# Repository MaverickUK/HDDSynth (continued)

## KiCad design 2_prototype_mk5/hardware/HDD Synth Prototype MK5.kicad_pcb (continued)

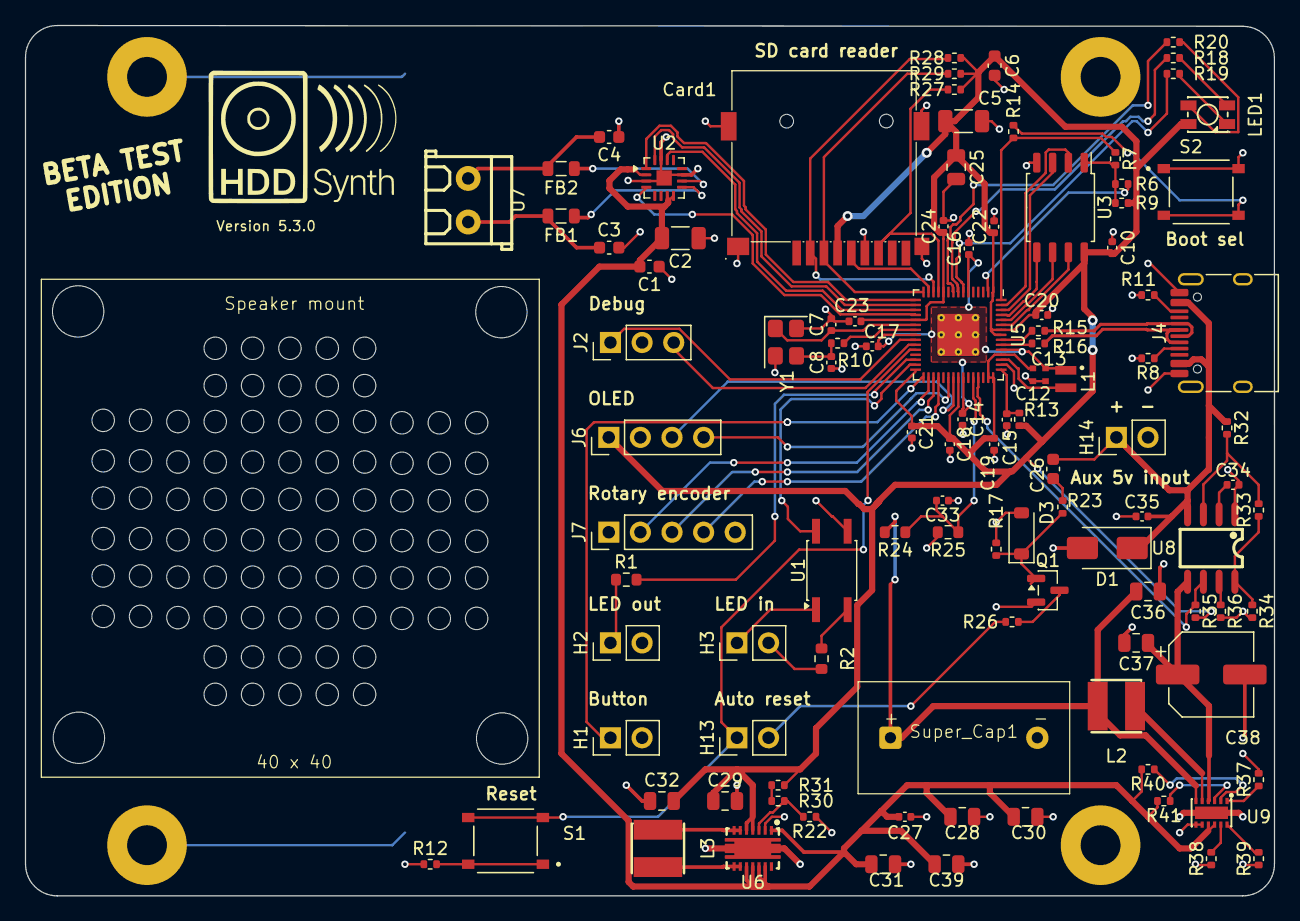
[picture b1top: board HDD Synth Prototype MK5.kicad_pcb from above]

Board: 2 copper layers, 100.3 x 69.9 mm, 110 parts (1 on the bottom side), 81 nets.

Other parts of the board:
 : LOGO; MHDDLA_Sound_40mm

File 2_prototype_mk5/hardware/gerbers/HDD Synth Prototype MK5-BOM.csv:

"Reference","Qty","Value","DNP","Exclude from BOM","Exclude from Board","LCSC Part Number","Footprint","Datasheet","Description"
"C1,C6,C26","3","0.1uF","","","","C14663","Capacitor_SMD:C_0603_1608Metric","","Unpolarized capacitor"
"C2,C5","2","10uF","","","","C13585","Capacitor_SMD:C_1206_3216Metric","","Unpolarized capacitor"
"C3,C4","2","1nF","","","","C1588","Capacitor_SMD:C_0603_1608Metric","","Unpolarized capacitor, small symbol"
"C7,C8","2","15p","","","","C1548","Capacitor_SMD:C_0402_1005Metric","",""
"C10,C14,C17,C18,C19,C20,C21,C22,C23,C24,C27,C33","12","100nF","","","","C1525","Capacitor_SMD:C_0402_1005Metric","",""
"C12,C13","2","4.7uF","","","","C23733","RP2350:C_0402_1005Metric_small_pads","",""
"C15,C16","2","4.7uF","","","","C23733","Capacitor_SMD:C_0402_1005Metric","",""
"C25,C28,C30,C36,C37","5","10uF","","","","C15850","Capacitor_SMD:C_0805_2012Metric","",""
"C29,C31,C32,C39","4","22uF","","","","C45783","Capacitor_SMD:C_0805_2012Metric","",""
"C34","1","4.7nF","","","","","Capacitor_SMD:C_0402_1005Metric","",""
"C35","1","1uF","","","","","Capacitor_SMD:C_0402_1005Metric","",""
"C38","1","100uF","","","","C134801","Capacitor_SMD:CP_Elec_6.3x7.7","","Polarized capacitor"
"Card1","1","TF-015","","","","C113206","easyeda2kicad:TF-SMD_TF-015","https://lcsc.com/product-detail/Card-Sockets_TF-015_C113206.html",""
"D1","1","SMAJ5.0A","","","","","Diode_SMD:D_SMA","","Zener diode"
"D3","1","1N4148W","","","","C81598","Diode_SMD:D_SOD-123","https://www.vishay.com/docs/85748/1n4148w.pdf","75V 0.15A Fast Switching Diode, SOD-123"
"FB1,FB2","2","FerriteBead_Small","","","","C85840","Inductor_SMD:L_0805_2012Metric","","Ferrite bead, small symbol"
"H1,H2,H3,H13,H14","5","Conn_01x02","","","","C124375","Connector_PinHeader_2.54mm:PinHeader_1x02_P2.54mm_Vertical","","Generic connector, single row, 01x02, script generated (kicad-library-utils/schlib/autogen/connector/)"
"J2","1","Conn_01x03","","","","C49257","Connector_PinHeader_2.54mm:PinHeader_1x03_P2.54mm_Vertical","","Generic connector, single row, 01x03, script generated (kicad-library-utils/schlib/autogen/connector/)"
"J4","1","USB_C_Receptacle_USB2.0_16P","","","","C165948","Connector_USB:USB_C_Receptacle_HRO_TYPE-C-31-M-12","","USB 2.0-only 16P Type-C Receptacle connector"
"J6","1","Conn_01x04_Pin","","","","C124378","Connector_PinHeader_2.54mm:PinHeader_1x04_P2.54mm_Vertical","","Generic connector, single row, 01x04, script generated"
"J7","1","Conn_01x05","","","","C124379","Connector_PinHeader_2.54mm:PinHeader_1x05_P2.54mm_Vertical","","Generic connector, single row, 01x05, script generated (kicad-library-utils/schlib/autogen/connector/)"
"L1","1","3.3u","","","","C42411119","RP2350:L_pol_2016","",""
"L2","1","2.2 µH","","","","C167804","easyeda2kicad:IND-SMD_L4.0-W4.0_FNR40XXS","","Inductor"
"L3","1","FNR4018S1R5MT","","","","C167802","easyeda2kicad:IND-SMD_L4.0-W4.0_FNR40XXS","https://lcsc.com/product-detail/Power-Inductors_1-5uH-20_C16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",""
"LED1","1","XL-3528RGBW-HM","","","","C2843813","Custom:LED-SMD_4P-L3.2-W2.8-LS3.5-XL-3528RGBW-HM5","https://www.lcsc.com/datasheet/C2843813.pdf",""
"Q1","1","2N7002","","","","C8545","Package_TO_SOT_SMD:SOT-23","https://www.onsemi.com/pub/Collateral/NDS7002A-D.PDF","0.115A Id, 60V Vds, N-Channel MOSFET, SOT-23"
"R1,R2","2","330R","","","","C23138","Resistor_SMD:R_0603_1608Metric","","Resistor"
"R7","1","0","","","","C17168","Resistor_SMD:R_0402_1005Metric","",""
"R8,R11","2","5.1K","","","","C25905","Resistor_SMD:R_0402_1005Metric","","Resistor"
"R10,R12,R14,R26","4","1K","","","","C11702","Resistor_SMD:R_0402_1005Metric","","Resistor"
"R13,R18,R20","3","33R","","","","C25105","Resistor_SMD:R_0402_1005Metric","","Resistor"
"R15,R16","2","27R","","","","C25100","Resistor_SMD:R_0402_1005Metric","",""
"R17,R30,R40,R41","4","100K","","","","C25741","Resistor_SMD:R_0402_1005Metric","","Resistor"
"R19","1","200R","","","","C25087","Resistor_SMD:R_0402_1005Metric","","Resistor"
"R22","1","22K","","","","C25768","Resistor_SMD:R_0402_1005Metric","","Resistor"
"R23,R35","2","10K","","","","C25744","Resistor_SMD:R_0402_1005Metric","","Resistor"
"R24,R25","2","22K","","","","C31850","Resistor_SMD:R_0603_1608Metric","","Resistor"
"R27,R28,R29,R33","4","47K","","","","C25792","Resistor_SMD:R_0402_1005Metric","","Resistor"
"R31","1","24K","","","","C25769","Resistor_SMD:R_0402_1005Metric","","Resistor"
"R32","1","330K","","","","C25778","Resistor_SMD:R_0402_1005Metric","","Resistor"
"R34","1","120K","","","","C25750","Resistor_SMD:R_0402_1005Metric","","Resistor"
"R36","1","110K","","","","C2909311","Resistor_SMD:R_0402_1005Metric","","Resistor"
"R37,R38,R39","3","75K","","","","C25798","Resistor_SMD:R_0402_1005Metric","","Resistor"
"S1,S2","2","TS-1187A-B-A-B","","","","C318884","Custom:SW_TS-1187A-B-A-B","","Tactile Switch SPST 160gf 1.5mm 5.1mm x 5.1mm Surface Mount"
"U1","1","Optocoupler_DC_PhotoNPN_AKEC","","","","C42381015","Package_SO:SO-4_4.4x3.6mm_P2.54mm","","Generic DC optocoupler with NPN phototransistor output, pins order: anode/cathode/emitter/collector"
"U2","1","MAX98357A","","","","C910544","Package_DFN_QFN:TQFN-16-1EP_3x3mm_P0.5mm_EP1.23x1.23mm","https://www.analog.com/media/en/technical-documentation/data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","Mono DAC with amplifier, I2S, PCM, TDM, 32-bit, 96khz, 3.2W, TQFP-16"
"U5","1","RP2350_60QFN","","","","C41378174","RP2350:RP2350-QFN-60-1EP_7x7_P0.4mm_EP3.4x3.4mm_ThermalVias","",""
"U6","1","TPS63020DSJR","","","","C15483","easyeda2kicad:VSON-14_L4.0-W3.0-P0.50-BL-EP_TI_DSJ","https://lcsc.com/product-detail/DC-DC-Converters_TI_TPS63020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",""
"U7","1","KF350-3.5-2P","","","","C474892","easyeda2kicad:CONN-TH_P3.50_KF350-3.5-2P","https://lcsc.com/product-detail/New-Quadratic-Unclassified-D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",""
"U8","1","TPS25921ADR","","","","C189199","easyeda2kicad:SOIC-8_L5.0-W4.0-P1.27-LS6.0-BL","https://lcsc.com/product-detail/PMIC-Supervisors_TI_TPS25921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",""
"U9","1","TPS61094DSSR","","","","C3034939","easyeda2kicad:WSON-12_L3.0-W2.0-P0.5-BL-EP","https://www.lcsc.com/datasheet/C3034939.pdf",""
"Y1","1","ABM8-272-T3","","","","C20617575","Crystal:Crystal_SMD_3225-4Pin_3.2x2.5mm","",""

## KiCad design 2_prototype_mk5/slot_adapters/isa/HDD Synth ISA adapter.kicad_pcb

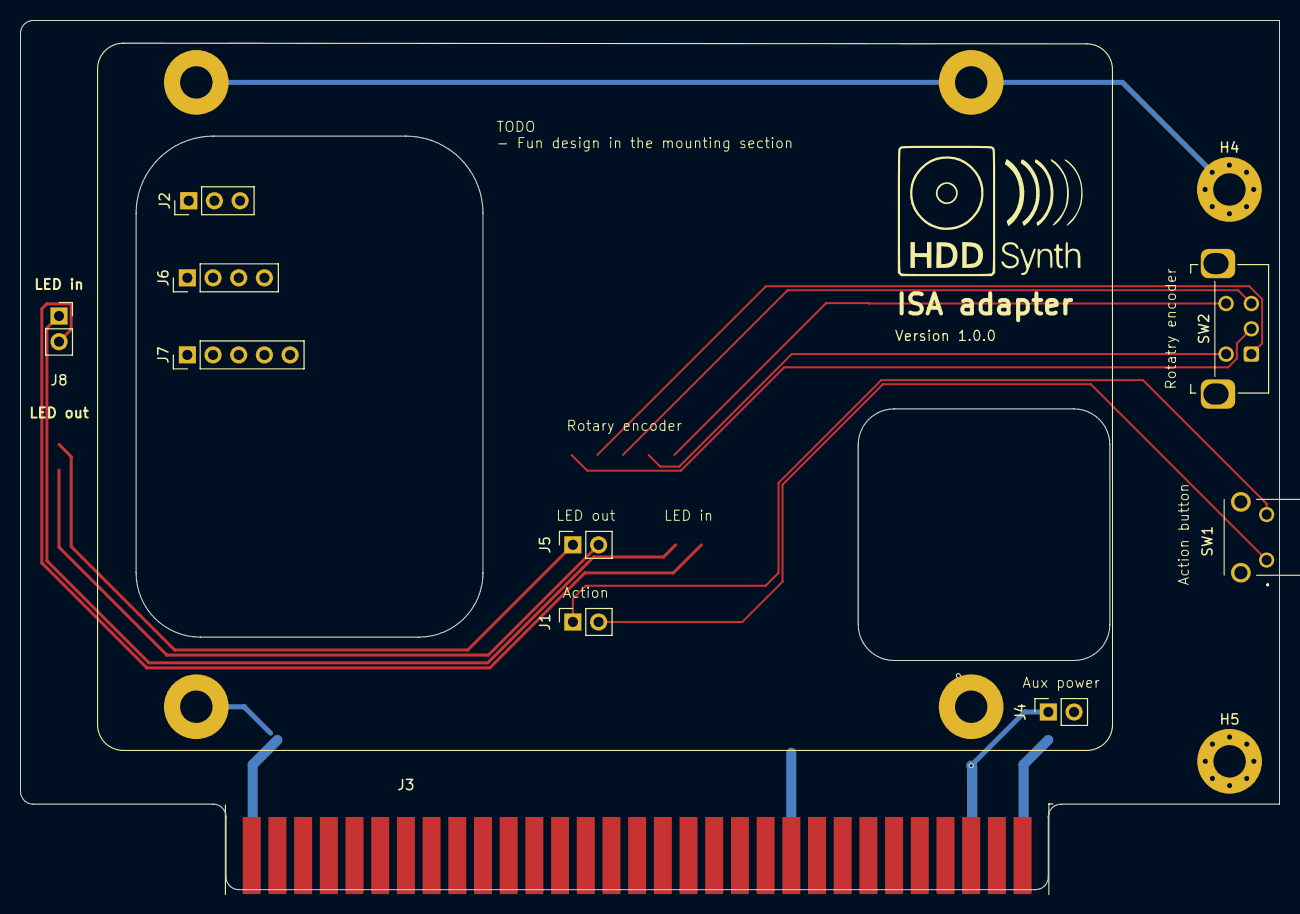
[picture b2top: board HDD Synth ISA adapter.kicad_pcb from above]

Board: 2 copper layers, 124.5 x 85.9 mm, 16 parts (0 on the bottom side), 4 nets.

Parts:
H4, H5: MountingHole_Pad; MountingHole_3.2mm_M3_Pad_Via
H8, H9, H10, H11: MountingHole_Pad; MountingHole_3.2mm_M3_Pad
J1, J4, J5, J8: Conn_01x02_Socket; PinSocket_1x02_P2.54mm_Vertical
J2: Conn_01x03; PinSocket_1x03_P2.54mm_Vertical
J3: Bus_ISA_8bit; BUS_AT_8bit
J6: Conn_01x04_Pin; PinSocket_1x04_P2.54mm_Vertical
J7: Conn_01x05; PinSocket_1x05_P2.54mm_Vertical
SW1: SW_Push; PTS645VL582LFS
SW2: PEC12R-2120F-S0012; RotaryEncoder_Bourns_Horizontal_PEC12R-2x17F-Sxxxx

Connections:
GND: H4.1 (1_1), H5.1 (1_1), H8.1 (1_1), H9.1 (1_1), H10.1 (1_1), H11.1 (1_1), J2.2, J3.1 (GND), J4.2, J6.2, J7.1, J7.5
unnamed: J1.1, SW1.2
unnamed: J1.2, SW1.1
unnamed: J3.3 (VCC), J4.1

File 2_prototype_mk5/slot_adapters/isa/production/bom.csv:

Designator,Footprint,Quantity,Value,LCSC Part #
"J1, J4",PinSocket_1x02_P2.54mm_Vertical,2,Conn_01x02_Socket,
J2,PinSocket_1x05_P2.54mm_Vertical,1,Conn_01x05_Socket,
SW1,PTS645VL582LFS,1,SW_Push,
SW2,RotaryEncoder_Bourns_Horizontal_PEC12R-2x17F-Sxxxx,1,PEC12R-2120F-S0012,

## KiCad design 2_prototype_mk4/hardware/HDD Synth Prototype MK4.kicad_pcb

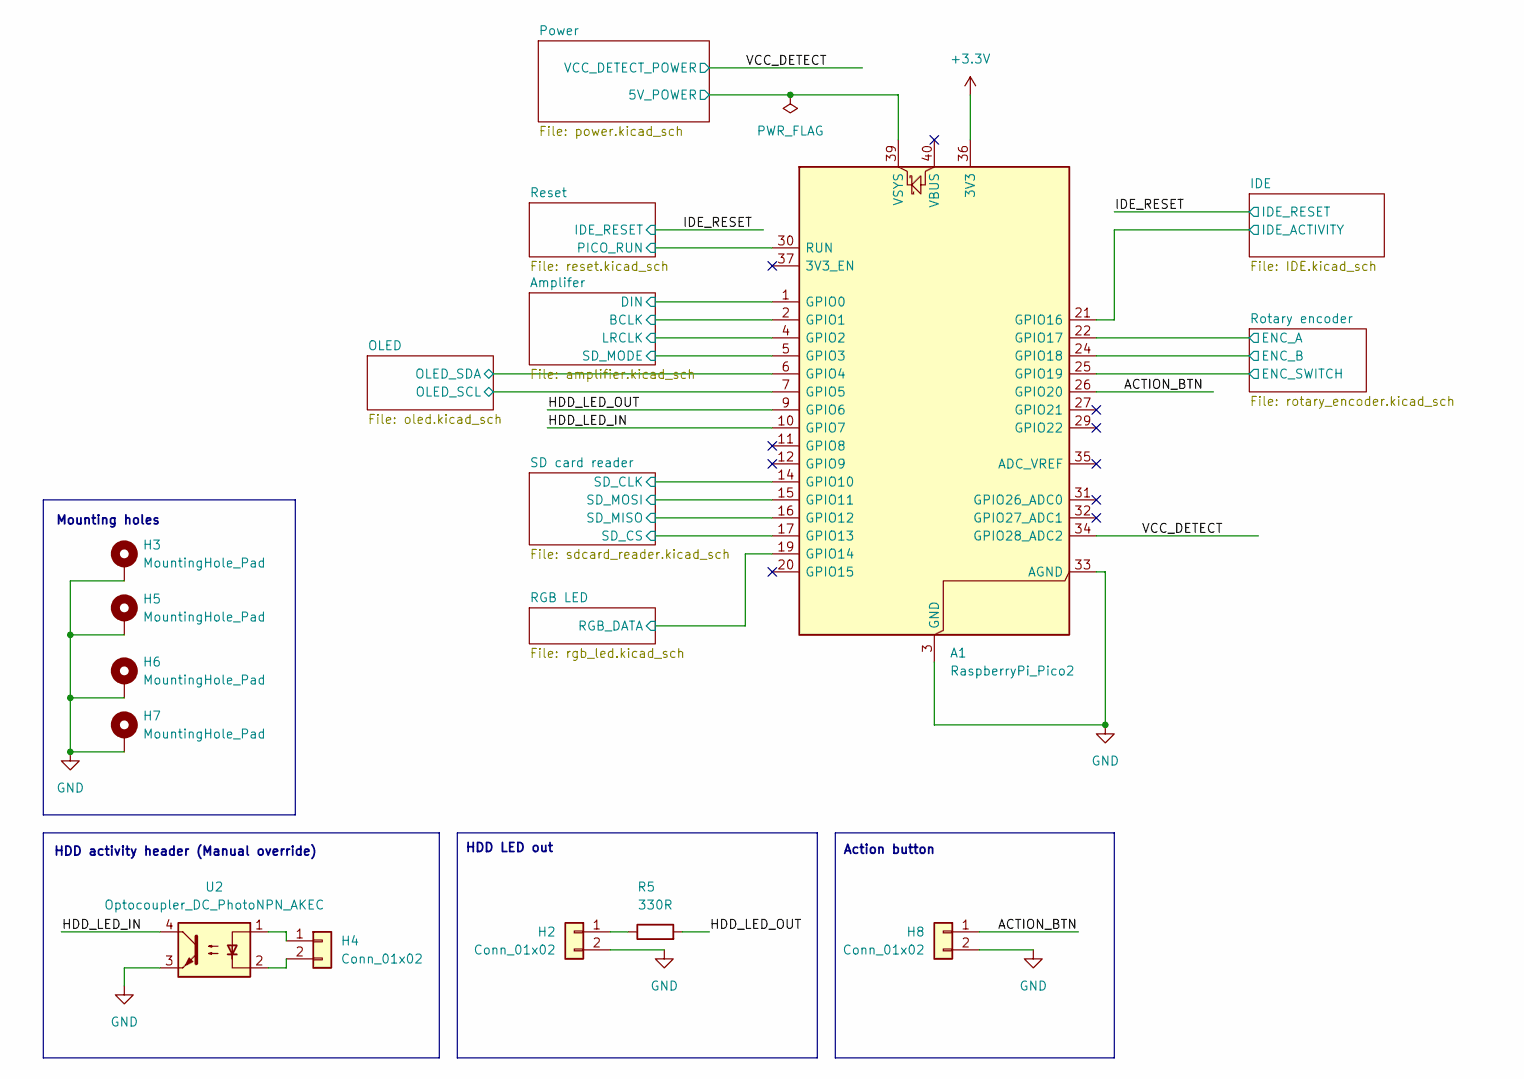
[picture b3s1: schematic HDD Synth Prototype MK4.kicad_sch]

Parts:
A1: RaspberryPi_Pico2; RaspberryPi_Pico_Common_Unspecified
H2, H4, H8: Conn_01x02; PinHeader_1x02_P2.54mm_Vertical
H3, H5, H6, H7: MountingHole_Pad; MountingHole_3.2mm_M3_Pad
R5: 330R; R_0603_1608Metric; Manufacturer_Part_Number RC0603FR-07330RL
U2: Optocoupler_DC_PhotoNPN_AKEC; SO-4_4.4x3.6mm_P2.54mm; Manufacturer_Part_Number EL357N(C)(TA)-VG; LCSC_Part_Number C2916312

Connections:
+3.3V: A1.36 (3V3); also elsewhere on the board
/ACTION_BTN: A1.26 (GPIO20), H8.1
/Amplifer/BCLK: A1.2 (GPIO1); also elsewhere on the board
/Amplifer/DIN: A1.1 (GPIO0); also elsewhere on the board
/Amplifer/LRCLK: A1.4 (GPIO2); also elsewhere on the board
/Amplifer/SD_MODE: A1.5 (GPIO3); also elsewhere on the board
/HDD_LED_IN: A1.10 (GPIO7), U2.4
/HDD_LED_OUT: A1.9 (GPIO6), R5.2
/IDE/IDE_ACTIVITY: A1.21 (GPIO16); also elsewhere on the board
/OLED/OLED_SCL: A1.7 (GPIO5); also elsewhere on the board
/OLED/OLED_SDA: A1.6 (GPIO4); also elsewhere on the board
/RGB LED/RGB_DATA: A1.19 (GPIO14); also elsewhere on the board
/Reset/PICO_RUN: A1.30 (RUN); also elsewhere on the board
/Rotary encoder/ENC_A: A1.22 (GPIO17); also elsewhere on the board
/Rotary encoder/ENC_B: A1.24 (GPIO18); also elsewhere on the board
/Rotary encoder/ENC_SWITCH: A1.25 (GPIO19); also elsewhere on the board
/SD card reader/SD_CLK: A1.14 (GPIO10); also elsewhere on the board
/SD card reader/SD_CS: A1.17 (GPIO13); also elsewhere on the board
/SD card reader/SD_MISO: A1.16 (GPIO12); also elsewhere on the board
/SD card reader/SD_MOSI: A1.15 (GPIO11); also elsewhere on the board
/VCC_DETECT: A1.34 (GPIO28_ADC2); also elsewhere on the board
GND: A1.3 (GND), A1.8 (GND), A1.13 (GND), A1.18 (GND), A1.23 (GND), A1.28 (GND), A1.33 (AGND), A1.38 (GND), H2.2, H3.1 (1_1), H5.1 (1_1), H6.1 (1_1), H7.1 (1_1), H8.2, U2.3; also elsewhere on the board
unnamed: H2.1, R5.1
unnamed: H4.1, U2.1
unnamed: H4.2, U2.2
POWER_5V_SUP: A1.39 (VSYS); also elsewhere on the board

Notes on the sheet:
Action button
Mounting holes
HDD activity header (Manual override)
HDD LED out

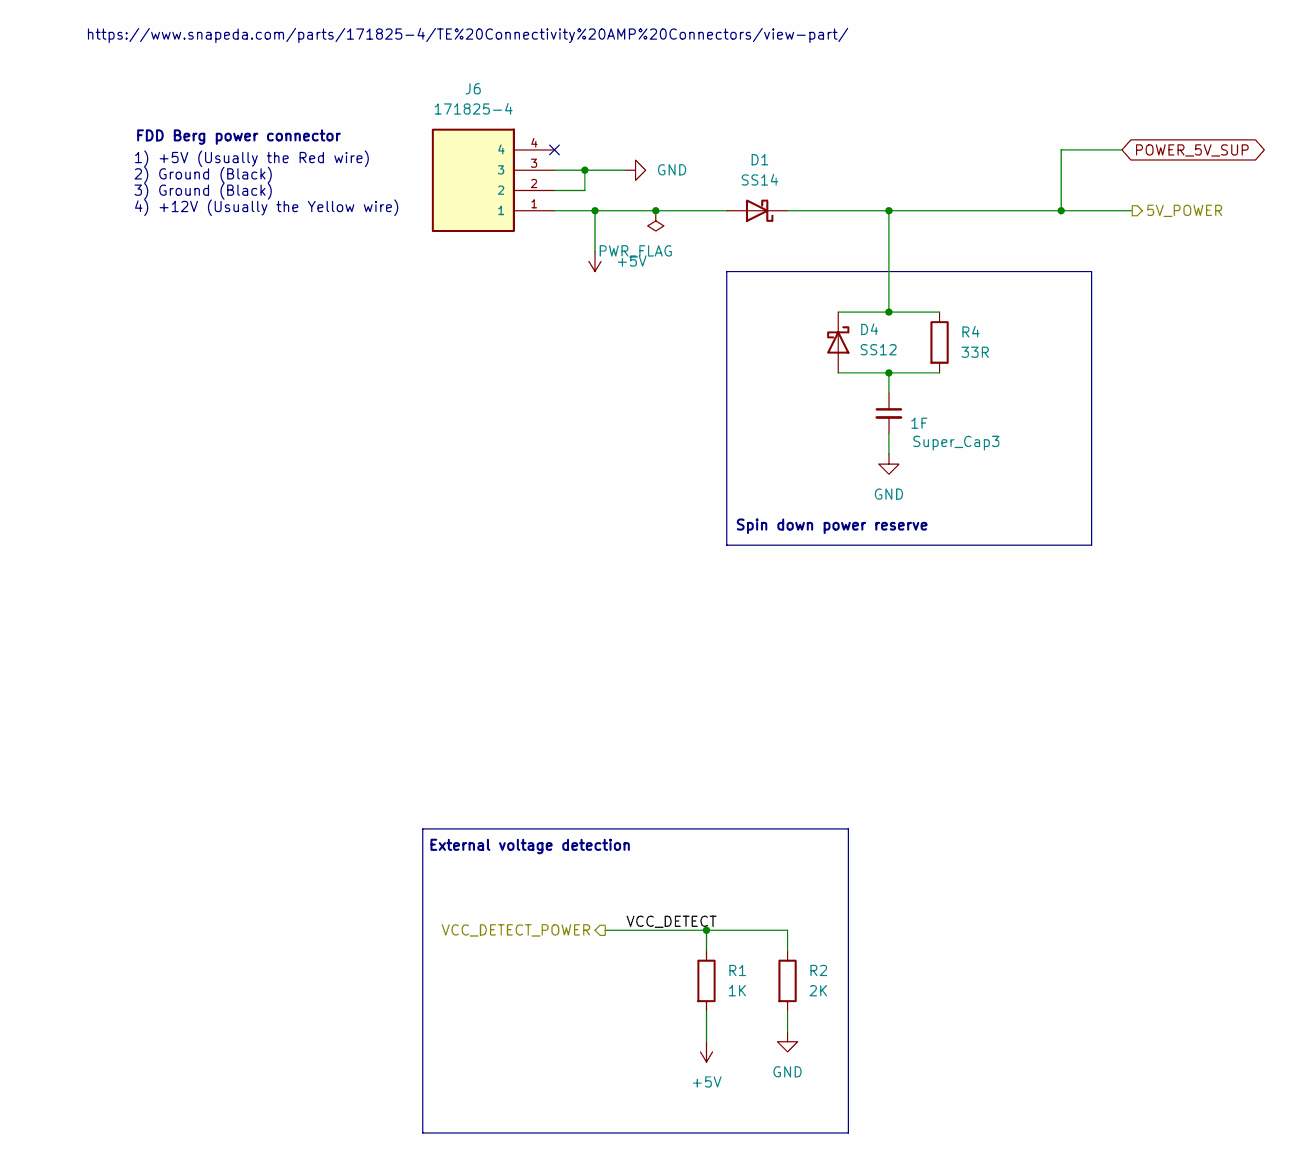
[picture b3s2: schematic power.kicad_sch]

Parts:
D1: SS14; D_SMA
D4: SS12; D_SMA; Manufacturer_Part_Number SS12; LCSC_Part_Number C184027
J6: 171825-4; TE_171825-4; PARTREV R
R1: 1K; R_0603_1608Metric; Manufacturer_Part_Number RC0603FR-071KL
R2: 2K; R_0603_1608Metric; Manufacturer_Part_Number RC0603FR-072KL
R4: 33R; R_1206_3216Metric; Manufacturer_Part_Number RC0603FR-0733RL
Super_Cap3: 1F; CP_Radial_D14.0mm_P5.00mm

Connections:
+5V: D1.2 (A), J6.1, R1.2
/VCC_DETECT: R1.1, R2.1; also elsewhere on the board
GND: J6.2, J6.3, R2.2, Super_Cap3.2; also elsewhere on the board
unnamed: D4.2 (A), R4.2, Super_Cap3.1
POWER_5V_SUP: D1.1 (K), D4.1 (K), R4.1; also elsewhere on the board

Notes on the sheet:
External voltage detection
FDD Berg power connector
https://www.snapeda.com/parts/171825-4/TE%20Connectivity%20AMP%20Connectors/view-part/
Spin down power reserve
1) +5V (Usually the Red wire) 2) Ground (Black) 3) Ground (Black) 4) +12V (Usually the Yellow wire)

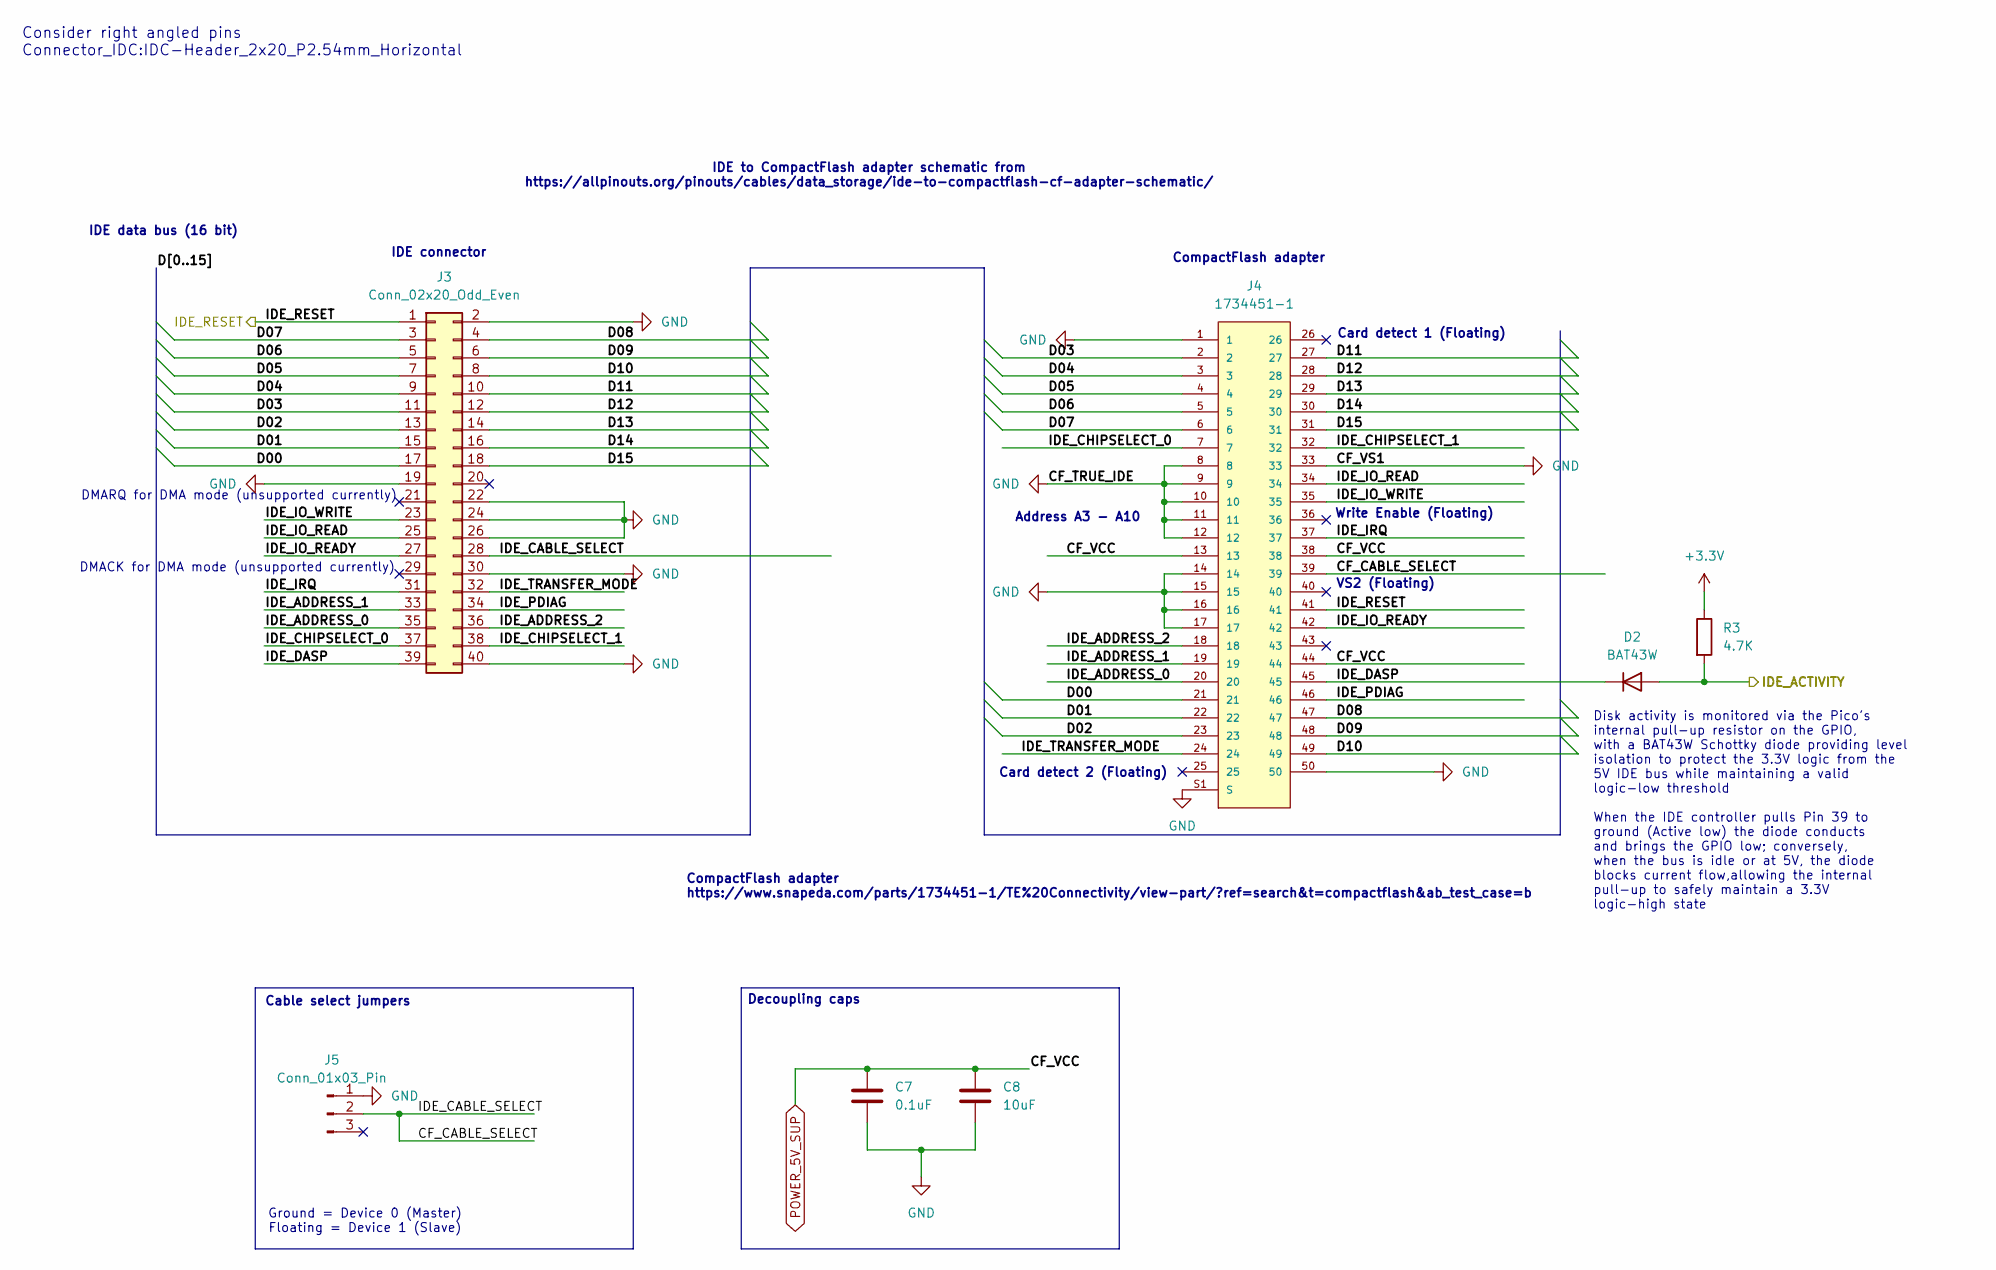
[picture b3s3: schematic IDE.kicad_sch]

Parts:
C7: 0.1uF; C_0603_1608Metric
C8: 10uF; C_1206_3216Metric
D2: BAT43W; D_SOD-123
J3: Conn_02x20_Odd_Even; IDC-Header_2x20_P2.54mm_Vertical
J4: 1734451-1; TE_1734451-1; PARTREV F
J5: Conn_01x03_Pin; PinHeader_1x03_P2.54mm_Vertical
R3: 4.7K; R_0603_1608Metric

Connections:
+3.3V: R3.1; also elsewhere on the board
/IDE/CF_CABLE_SELECT: J3.28, J4.39, J5.2
/IDE/D00: J3.17, J4.21
/IDE/D01: J3.15, J4.22
/IDE/D02: J3.13, J4.23
/IDE/D03: J3.11, J4.2
/IDE/D04: J3.9, J4.3
/IDE/D05: J3.7, J4.4
/IDE/D06: J3.5, J4.5
/IDE/D07: J3.3, J4.6
/IDE/D08: J3.4, J4.47
/IDE/D09: J3.6, J4.48
/IDE/D10: J3.8, J4.49
/IDE/D11: J3.10, J4.27
/IDE/D12: J3.12, J4.28
/IDE/D13: J3.14, J4.29
/IDE/D14: J3.16, J4.30
/IDE/D15: J3.18, J4.31
/IDE/IDE_ACTIVITY: D2.2 (A), R3.2; also elsewhere on the board
/IDE/IDE_ADDRESS_0: J3.35, J4.20
/IDE/IDE_ADDRESS_1: J3.33, J4.19
/IDE/IDE_ADDRESS_2: J3.36, J4.18
/IDE/IDE_CHIPSELECT_0: J3.37, J4.7
/IDE/IDE_CHIPSELECT_1: J3.38, J4.32
/IDE/IDE_DASP: D2.1 (K), J3.39, J4.45
/IDE/IDE_IO_READ: J3.25, J4.34
/IDE/IDE_IO_READY: J3.27, J4.42
/IDE/IDE_IO_WRITE: J3.23, J4.35
/IDE/IDE_IRQ: J3.31, J4.37
/IDE/IDE_PDIAG: J3.34, J4.46
/IDE/IDE_TRANSFER_MODE: J3.32, J4.24
/IDE_RESET: J3.1, J4.41; also elsewhere on the board
GND: C7.2, C8.2, J3.2, J3.19, J3.22, J3.24, J3.26, J3.30, J3.40, J4.1, J4.8, J4.9, J4.10, J4.11, J4.12, J4.14, J4.15, J4.16, J4.17, J4.33, J4.50, J4.S1 (S), J4.S2 (S), J5.1; also elsewhere on the board
POWER_5V_SUP: C7.1, C8.1, J4.13, J4.38, J4.44; also elsewhere on the board

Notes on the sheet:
Disk activity is monitored via the Pico's internal pull-up resistor on the GPIO, with a BAT43W Schottky diode providing level isolation to protect the 3.3V logic from the 5V IDE bus while maintaining a valid logic-low threshold When the IDE controller pulls Pin 39 to ground (Active low) the diode c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
CompactFlash adapter
VS2 (Floating)
Write Enable (Floating)
IDE data bus (16 bit)
IDE to CompactFlash adapter schematic from https://allpinouts.org/pinouts/cables/data_storage/ide-to-compactflash-cf-adapter-schematic/
Ground = Device 0 (Master) Floating = Device 1 (Slave)
Decoupling caps
Card detect 2 (Floating)
Address A3 - A10
Cable select jumpers
Card detect 1 (Floating)
DMACK for DMA mode (unsupported currently)
CompactFlash adapter https://www.snapeda.com/parts/1734451-1/TE%20Connectivity/view-part/?ref=search&t=compactflash&ab_test_case=b
DMARQ for DMA mode (unsupported currently)
Consider right angled pins Connector_IDC:IDC-Header_2x20_P2.54mm_Horizontal
IDE connector

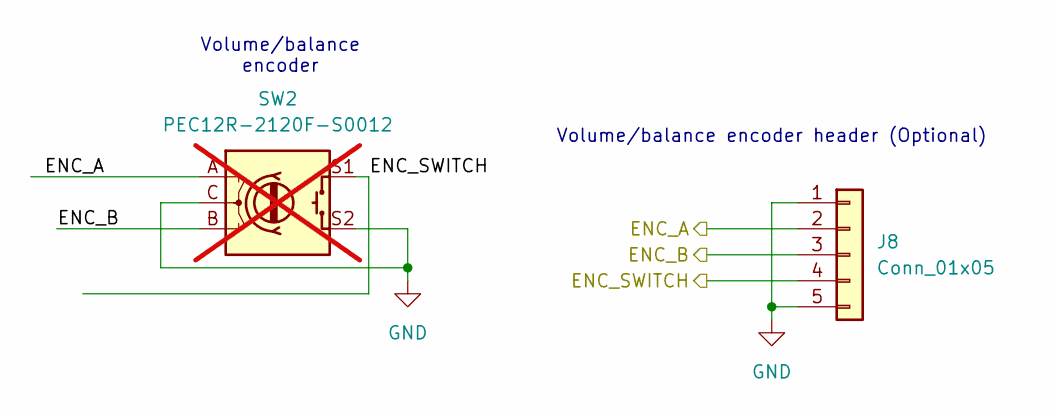
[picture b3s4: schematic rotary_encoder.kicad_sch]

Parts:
J8: Conn_01x05; PinHeader_1x05_P2.54mm_Vertical
SW2: PEC12R-2120F-S0012; RotaryEncoder_Bourns_Horizontal_PEC12R-2x17F-Sxxxx; Manufacturer_Part_Number PEC12R-2120F-S0012; LCSC_Part_Number PEC12R-2220F-S0024; not fitted

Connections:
/Rotary encoder/ENC_A: J8.2; also elsewhere on the board
/Rotary encoder/ENC_B: J8.3; also elsewhere on the board
/Rotary encoder/ENC_SWITCH: J8.4; also elsewhere on the board
GND: J8.1, J8.5, SW2.C, SW2.S2; also elsewhere on the board

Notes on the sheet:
Volume/balance encoder
Volume/balance encoder header (Optional)

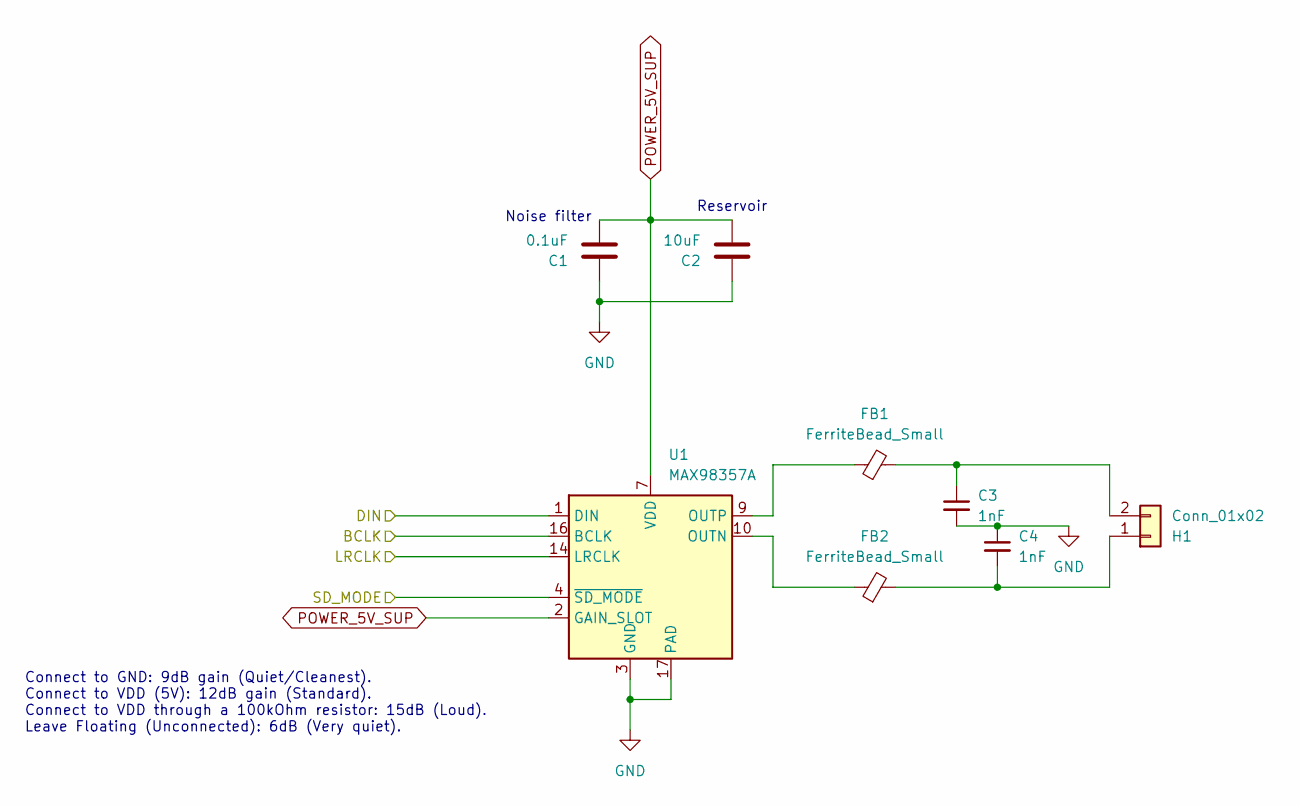
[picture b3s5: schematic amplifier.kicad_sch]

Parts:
C1: 0.1uF; C_0603_1608Metric; Manufacturer_Part_Number CL10B104KO8NNNC
C2: 10uF; C_1206_3216Metric; Manufacturer_Part_Number CL31A106KAHNNNE
C3, C4: 1nF; C_0603_1608Metric; Manufacturer_Part_Number 0603B102K500NT
FB1, FB2: FerriteBead_Small; L_0805_2012Metric; Manufacturer_Part_Number BLM21PG221SN1D; LCSC_Part_Number C85840
H1: Conn_01x02; TerminalBlock_Phoenix_PT-1,5-2-3.5-H_1x02_P3.50mm_Horizontal; Manufacturer_Part_Number 1984617; LCSC_Part_Number C3819527
U1: MAX98357A; TQFN-16-1EP_3x3mm_P0.5mm_EP1.23x1.23mm; Manufacturer_Part_Number MAX98357AETE+T; LCSC_Part_Number C910544

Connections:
/Amplifer/BCLK: U1.16 (BCLK); also elsewhere on the board
/Amplifer/DIN: U1.1 (DIN); also elsewhere on the board
/Amplifer/LRCLK: U1.14 (LRCLK); also elsewhere on the board
/Amplifer/SD_MODE: U1.4 (~SD_MODE); also elsewhere on the board
GND: C1.1, C2.1, C3.2, C4.1, U1.3 (GND), U1.11 (GND), U1.15 (GND), U1.17 (PAD); also elsewhere on the board
unnamed: C4.2, FB2.2, H1.1
unnamed: C3.1, FB1.2, H1.2
unnamed: FB2.1, U1.10 (OUTN)
unnamed: FB1.1, U1.9 (OUTP)
POWER_5V_SUP: C1.2, C2.2, U1.2 (GAIN_SLOT), U1.7 (VDD), U1.8 (VDD); also elsewhere on the board

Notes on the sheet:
Connect to GND: 9dB gain (Quiet/Cleanest). Connect to VDD (5V): 12dB gain (Standard). Connect to VDD through a 100kOhm resistor: 15dB (Loud). Leave Floating (Unconnected): 6dB (Very quiet).
Reservoir
Noise filter

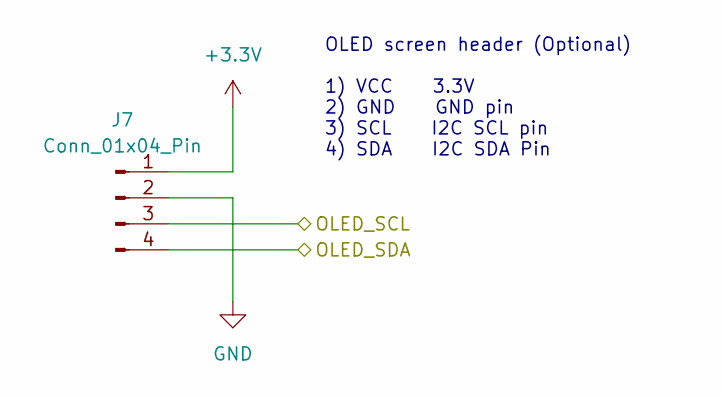
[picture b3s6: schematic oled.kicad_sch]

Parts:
J7: Conn_01x04_Pin; PinHeader_1x04_P2.54mm_Vertical

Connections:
+3.3V: J7.1; also elsewhere on the board
/OLED/OLED_SCL: J7.3; also elsewhere on the board
/OLED/OLED_SDA: J7.4; also elsewhere on the board
GND: J7.2; also elsewhere on the board

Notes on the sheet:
OLED screen header (Optional) 1) VCC 3.3V 2) GND GND pin 3) SCL I2C SCL pin 4) SDA I2C SDA Pin

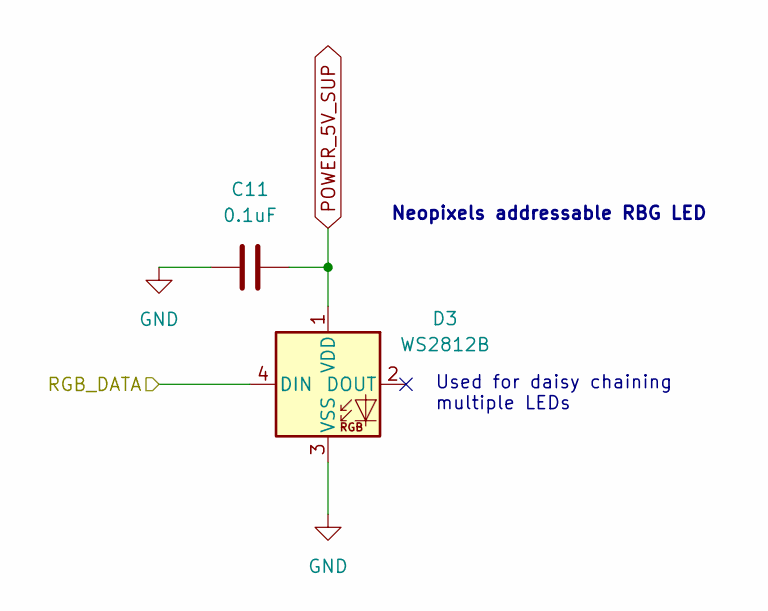
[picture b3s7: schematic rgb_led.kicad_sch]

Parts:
C11: 0.1uF; C_0603_1608Metric; Manufacturer_Part_Number CL10B104KO8NNNC
D3: WS2812B; LED_WS2812B_PLCC4_5.0x5.0mm_P3.2mm

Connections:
/RGB LED/RGB_DATA: D3.4 (DIN); also elsewhere on the board
GND: C11.1, D3.3 (VSS); also elsewhere on the board
POWER_5V_SUP: C11.2, D3.1 (VDD); also elsewhere on the board

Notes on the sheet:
Used for daisy chaining multiple LEDs
Neopixels addressable RBG LED

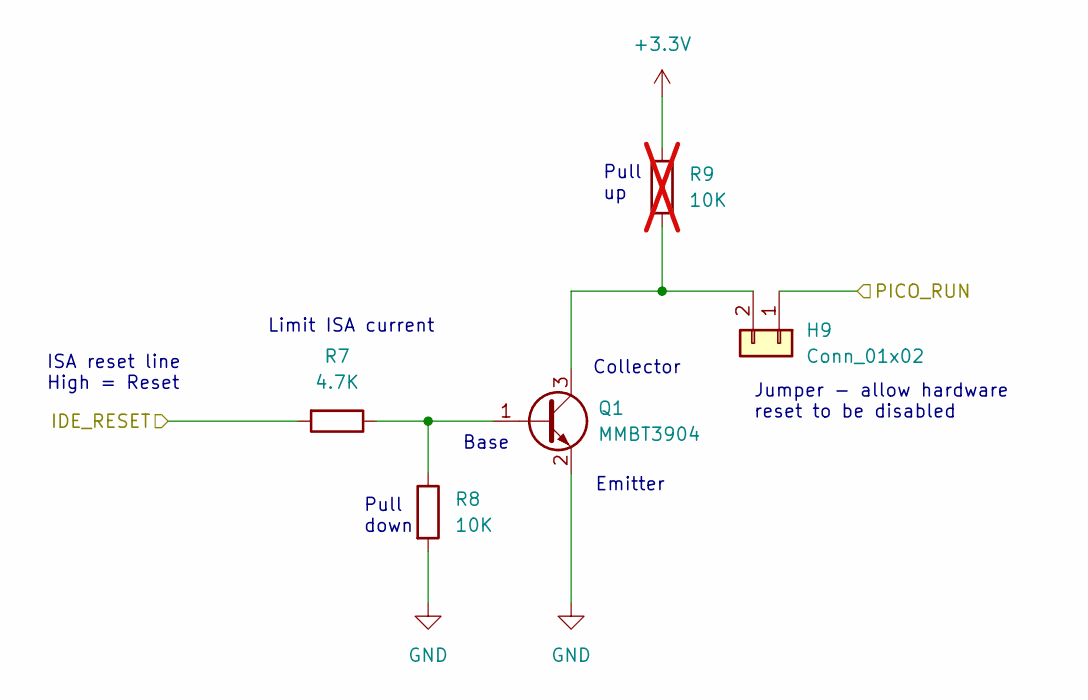
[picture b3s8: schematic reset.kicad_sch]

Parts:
H9: Conn_01x02; PinHeader_1x02_P2.54mm_Vertical
Q1: MMBT3904; SOT-23
R7: 4.7K; R_0402_1005Metric
R8: 10K; R_0402_1005Metric
R9: 10K; R_0402_1005Metric; not fitted

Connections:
/IDE_RESET: R7.2; also elsewhere on the board
/Reset/PICO_RUN: H9.1; also elsewhere on the board
GND: Q1.2 (E), R8.2; also elsewhere on the board
unnamed: H9.2, Q1.3 (C), R9.2
unnamed: Q1.1 (B), R7.1, R8.1

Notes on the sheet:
Pull down
Limit ISA current
Jumper - allow hardware reset to be disabled
Pull up
Emitter
ISA reset line High = Reset
Collector
Base

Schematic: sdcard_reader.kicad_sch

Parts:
C5: 10uF; C_1206_3216Metric; Manufacturer_Part_Number CL31A106KAHNNNE
C6: 0.1uF; C_0603_1608Metric; Manufacturer_Part_Number CL10B104KO8NNNC
J1: Micro_SD_Card; microSD_HC_Hirose_DM3D-SF; Manufacturer_Part_Number DM3D-SF; LCSC_Part_Number C719027
RN1: 47K; R_Array_Convex_4x0603; Manufacturer_Part_Number YC164-JR-0747KL; LCSC_Part_Number C779384

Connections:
+3.3V: C5.1, C6.1, J1.4 (VDD), RN1.6 (R3.2), RN1.7 (R2.2), RN1.8 (R1.2); also elsewhere on the board
/SD card reader/SD_CLK: J1.5 (CLK); also elsewhere on the board
/SD card reader/SD_CS: J1.2 (DAT3/CD), RN1.1 (R1.1); also elsewhere on the board
/SD card reader/SD_MISO: J1.7 (DAT0), RN1.3 (R3.1); also elsewhere on the board
/SD card reader/SD_MOSI: J1.3 (CMD), RN1.2 (R2.1); also elsewhere on the board
GND: C5.2, C6.2, J1.6 (VSS), J1.9 (SHIELD); also elsewhere on the board

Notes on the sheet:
Master In, Slave Out
Pull ups
Filter
Chip select
Master out, Slave in
Reservour
Serial clock
Hirose DM3D-SF Manual push/pull Ideal for internal use
